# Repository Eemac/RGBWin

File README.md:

# RGBWin!!
A kW-scale RGBW LED controller for indoor effect lighting. I designed this board in my sophomore year of high school because no low-cost, highly-programmable RGBW solution existed at the time. The two TSSOP parts (PCA9685 16ch PWM controllers) were the first SMT parts I soldered. 

## Schematic
My second time using Autodesk Eagle. I didn't know pin labels were a thing, so all wires are directly routed from input to output. I'm so sorry! :P Also, an interesting story about the big power MOSFETs: the only ones I could find that were in my budget came from an obscure eBay listing. I ended up waiting about a month just to put the final parts on the board because shipping took so long! 

## PCB
A fairly decent design, I think. I didn't know about ground pours at the time, so I manually routed large ground traces to all of the power MOSFETs.

## Design Files/Code, should anyone want.
Provided in the `project` folder.
The Arduino code includes two libraries: `Thread` (https://www.arduino.cc/reference/en/libraries/thread/), and `PCA9685` (https://www.arduino.cc/reference/en/libraries/pca9685-16-channel-pwm-driver-module-library/). These two links have installation instructions and are supported by the Arduino Library manager.

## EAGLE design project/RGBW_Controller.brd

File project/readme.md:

# Project files

Eagle board/schematic files included as well as a test Arduino .ino file

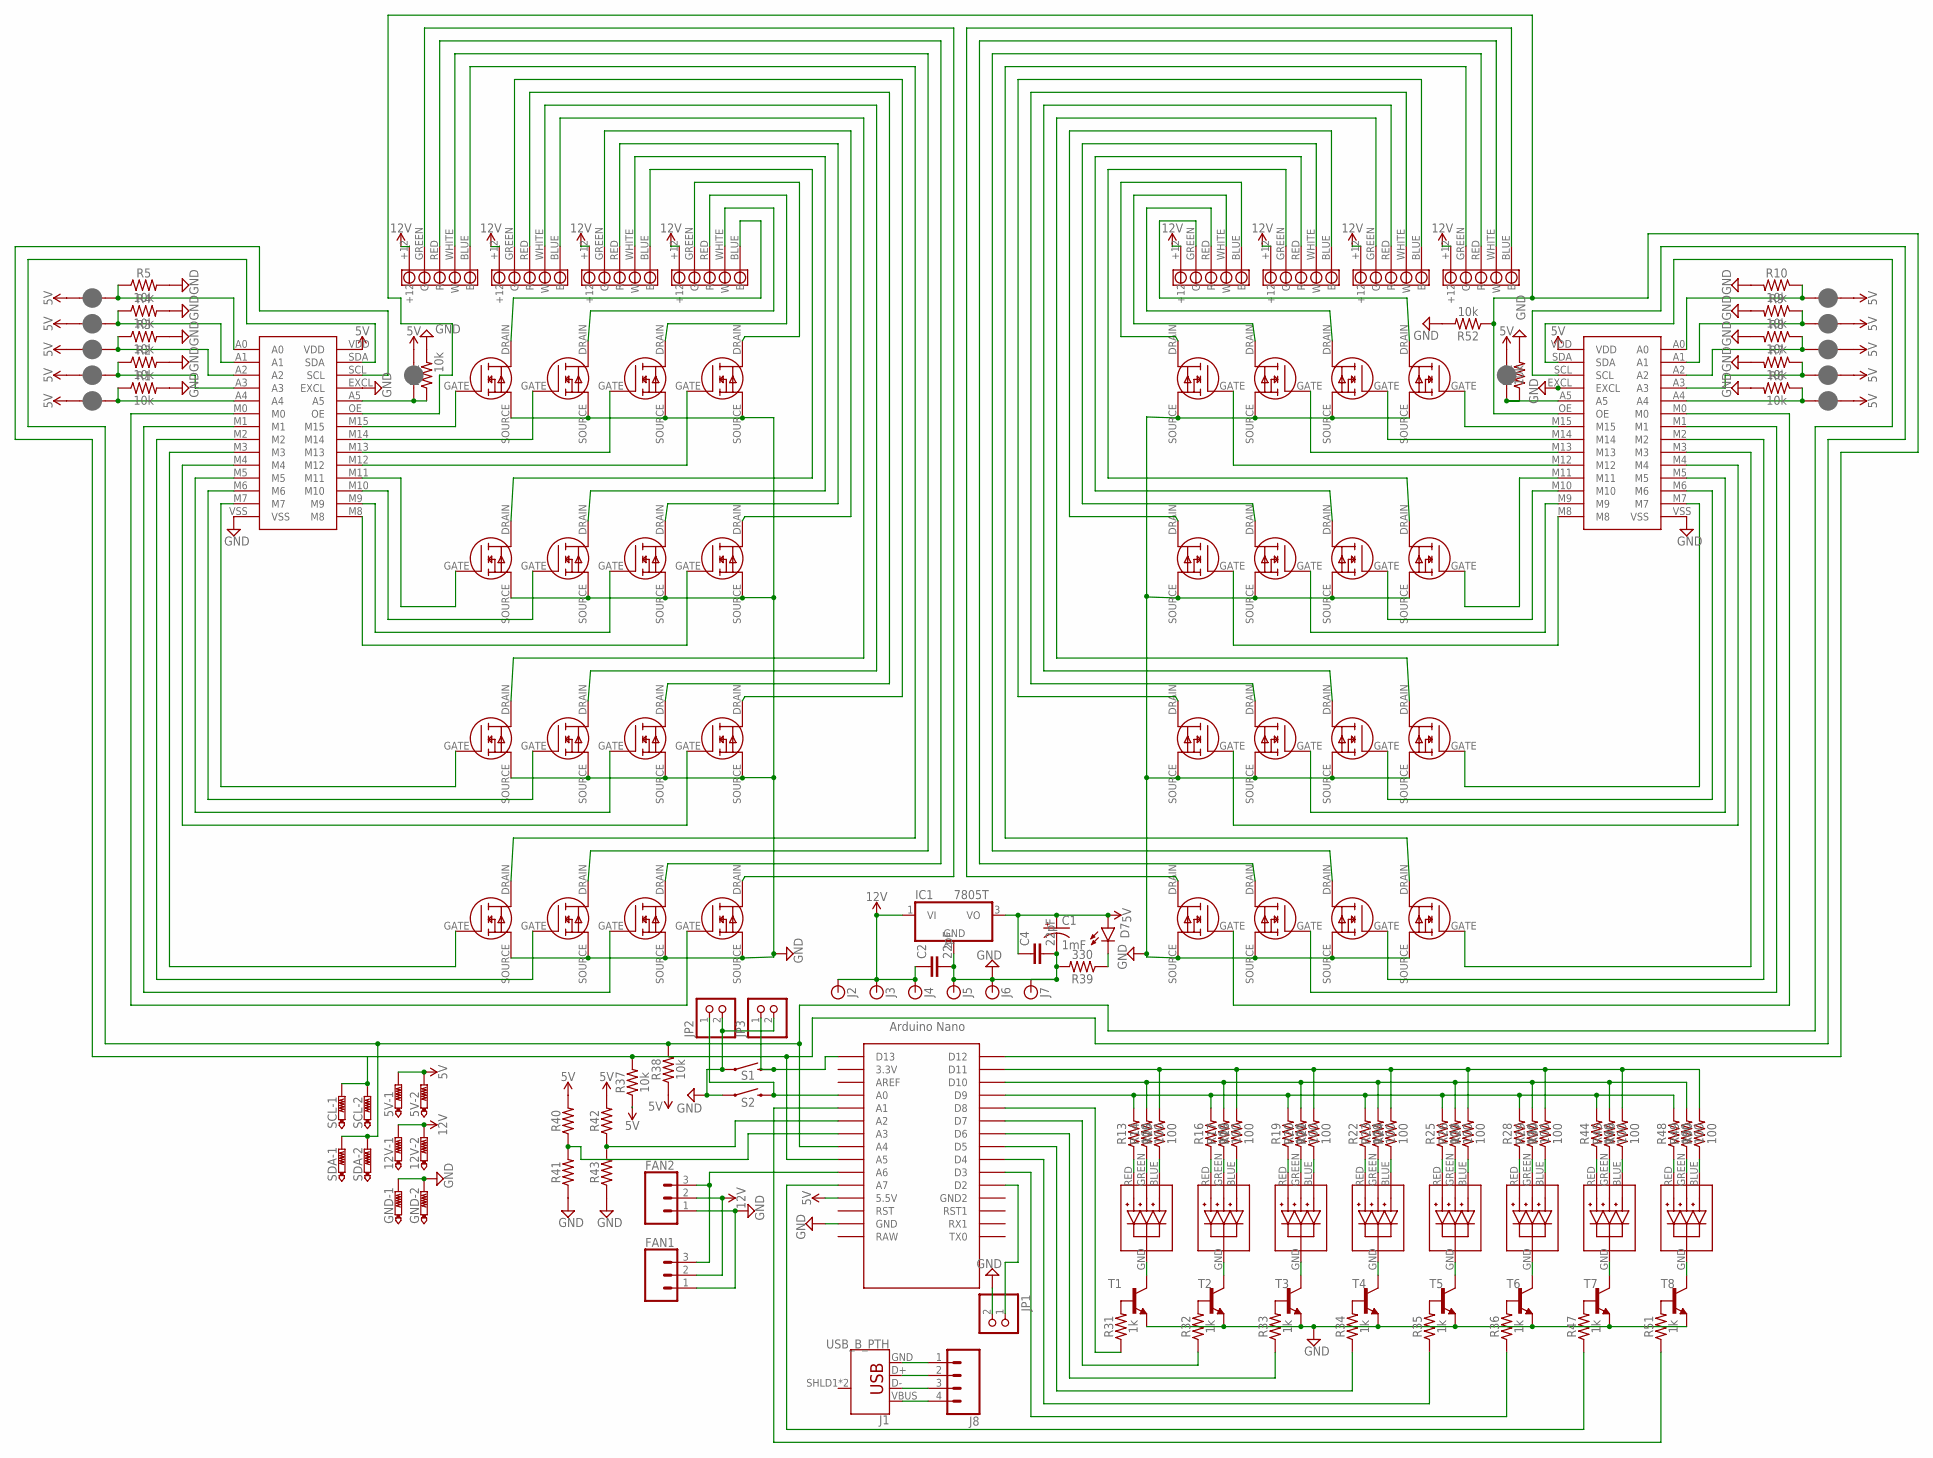
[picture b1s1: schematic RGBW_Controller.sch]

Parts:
5V, 12V: PTR2; P2-38-17
C1: 1mF; CPOL-RADIAL-5MM-10MM
C2, C4: 22pF; CAP-PTH-2.54
D7: LED5MM; LED_5MM
FAN1, FAN2: CONN_03; 1X03
GND: PTR2; P2-38-17
IC1: 7805T; TO220H
J1: USB_B_PTH; USB-B-PTH
J1_, J2_, J3_, J4_, J5_, J6_, J7_, J8_, J9_, J10_, J11_, J12_: JUMPER-SMT_2_NC_PASTE_SILK; SMT-JUMPER_2_NC_PASTE_SILK
J2, J3, J4, J5, J6, J7: BANANA_CONN
J8: CONN_04; 1X04
JP1, JP2, JP3: PINHD-1X2; 1X02
R1, R2, R3, R4, R5, R6, R7, R8, R9, R10, R11, R12, R37, R38, R52: 10k; AXIAL-0.3
R13, R14, R15, R16, R17, R18, R19, R20, R21, R22, R23, R24, R25, R26, R27, R28, R29, R30, R44, R45, R46, R48, R49, R50: 100; AXIAL-0.3
R31, R32, R33, R34, R35, R36, R47, R51: 1k; AXIAL-0.3
R39: 330; AXIAL-0.3
R40, R42: 10; AXIAL-0.1
R41, R43: 10; AXIAL-0.3
S1, S2: MOMENTARY-SWITCH-SPST-PTH-6.0MM; TACTILE_SWITCH_PTH_6.0MM
SCL: PTR2; P2-38-17
SDA: PTR2; P2-38-17
T1, T2, T3, T4, T5, T6, T7, T8: -NPN-TO92-EBC; TO92-EBC
U$1, U$18: 16CH_PWM
U$2, U$3, U$4, U$5, U$6, U$7, U$8, U$9, U$10, U$11, U$12, U$13, U$14, U$15, U$16, U$17, U$19, U$20, U$21, U$22, U$23, U$24, U$25, U$26, U$27, U$28, U$29, U$30, U$31, U$32, U$33, U$34: MOSFET
U$35: NANO
U$36, U$45, U$46, U$47, U$48, U$49, U$50, U$51: 5MM_RGB; 5MMRGB
U$37, U$38, U$39, U$40, U$41, U$42, U$43, U$44: 5POLE_TERM

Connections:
5V: 5V.TP-1, 5V.TP-2, C1.+, C4.1, D7.A, IC1.3 (VO), J1_.1, J2_.1, J3_.1, J4_.1, J5_.1, J6_.1, J7_.1, J8_.1, J9_.1, J10_.1, J11_.1, J12_.1, R37.P$1 (1), R38.P$1 (1), R40.P$2 (2), R42.P$2 (2), U$1.VDD, U$18.VDD, U$35.5V (5.5V)
12V: 12V.TP-1, 12V.TP-2, C2.1, FAN1.2, FAN2.2, IC1.1 (VI), J2.P$1, J3.P$1, J4.P$1, U$37.+12, U$38.+12, U$39.+12, U$40.+12, U$41.+12, U$42.+12, U$43.+12, U$44.+12
GND: C1.-, C2.2, C4.2, FAN1.1, FAN2.1, GND.TP-1, GND.TP-2, IC1.2 (GND), J5.P$1, J6.P$1, J7.P$1, JP1.2, JP2.2, JP3.2, R1.P$2 (2), R2.P$2 (2), R3.P$2 (2), R4.P$2 (2), R5.P$2 (2), R6.P$2 (2), R7.P$2 (2), R8.P$2 (2), R9.P$2 (2), R10.P$2 (2), R11.P$2 (2), R12.P$2 (2), R39.P$2 (2), R41.P$1 (1), R43.P$1 (1), R52.P$2 (2), S1.1, S2.1, T1.E, T2.E, T3.E, T4.E, T5.E, T6.E, T7.E, T8.E, U$1.EXCL, U$1.VSS, U$2.SOURCE, U$3.SOURCE, U$4.SOURCE, U$5.SOURCE, U$6.SOURCE, U$7.SOURCE, U$8.SOURCE, U$9.SOURCE, U$10.SOURCE, U$11.SOURCE, U$12.SOURCE, U$13.SOURCE, U$14.SOURCE, U$15.SOURCE, U$16.SOURCE, U$17.SOURCE, U$18.EXCL, U$18.VSS, U$19.SOURCE, U$20.SOURCE, U$21.SOURCE, U$22.SOURCE, U$23.SOURCE, U$24.SOURCE, U$25.SOURCE, U$26.SOURCE, U$27.SOURCE, U$28.SOURCE, U$29.SOURCE, U$30.SOURCE, U$31.SOURCE, U$32.SOURCE, U$33.SOURCE, U$34.SOURCE, U$35.GND
unnamed: J12_.2, R12.P$1 (1), U$18.A5
unnamed: R15.P$2 (2), R18.P$2 (2), R21.P$2 (2), R24.P$2 (2), R27.P$2 (2), R30.P$2 (2), R46.P$2 (2), R50.P$2 (2), U$35.D11
unnamed: R13.P$1 (1), U$36.RED
unnamed: R14.P$1 (1), U$36.GREEN
unnamed: J6_.2, R11.P$1 (1), U$1.A5
unnamed: R15.P$1 (1), U$36.BLUE
unnamed: U$18.M15, U$19.GATE
unnamed: U$18.M14, U$20.GATE
unnamed: U$18.M13, U$21.GATE
unnamed: U$1.M15, U$2.GATE
unnamed: U$1.M14, U$3.GATE
unnamed: U$1.M13, U$4.GATE
unnamed: U$1.M12, U$5.GATE
unnamed: D7.K (C), R39.P$1 (1)
unnamed: U$2.DRAIN, U$43.BLUE (B)
unnamed: R16.P$1 (1), U$45.RED
unnamed: R17.P$1 (1), U$45.GREEN
unnamed: J1_.2, R5.P$1 (1), U$1.A0
unnamed: U$1.M11, U$6.GATE
unnamed: U$1.M10, U$7.GATE
unnamed: U$1.M9, U$8.GATE
unnamed: U$1.M8, U$9.GATE
unnamed: R18.P$1 (1), U$45.BLUE
unnamed: R19.P$1 (1), U$46.RED
unnamed: R20.P$1 (1), U$46.GREEN
unnamed: R21.P$1 (1), U$46.BLUE
unnamed: U$18.M12, U$22.GATE
unnamed: U$1.M7, U$10.GATE
unnamed: U$1.M6, U$11.GATE
unnamed: U$1.M5, U$12.GATE
unnamed: U$1.M4, U$13.GATE
unnamed: R22.P$1 (1), U$47.RED
unnamed: R23.P$1 (1), U$47.GREEN
unnamed: R24.P$1 (1), U$47.BLUE
unnamed: R25.P$1 (1), U$48.RED
unnamed: U$22.DRAIN, U$44.BLUE (B)
unnamed: U$1.M3, U$14.GATE
unnamed: U$1.M2, U$15.GATE
unnamed: U$1.M1, U$16.GATE
unnamed: U$1.M0, U$17.GATE
unnamed: R26.P$1 (1), U$48.GREEN
unnamed: R27.P$1 (1), U$48.BLUE
unnamed: R28.P$1 (1), U$49.RED
unnamed: R29.P$1 (1), U$49.GREEN
unnamed: U$21.DRAIN, U$44.WHITE (W)
unnamed: U$20.DRAIN, U$44.RED (R)
unnamed: U$19.DRAIN, U$44.GREEN (G)
unnamed: J2_.2, R4.P$1 (1), U$1.A1
unnamed: U$18.M11, U$23.GATE
unnamed: U$18.M10, U$24.GATE
unnamed: U$18.M9, U$25.GATE
unnamed: U$18.M8, U$26.GATE
unnamed: U$26.DRAIN, U$42.BLUE (B)
unnamed: U$25.DRAIN, U$42.WHITE (W)
unnamed: U$24.DRAIN, U$42.RED (R)
unnamed: U$23.DRAIN, U$42.GREEN (G)
unnamed: U$18.M7, U$27.GATE
unnamed: U$18.M6, U$28.GATE
unnamed: U$18.M5, U$29.GATE
unnamed: U$18.M4, U$30.GATE
unnamed: U$30.DRAIN, U$41.BLUE (B)
unnamed: U$29.DRAIN, U$41.WHITE (W)
unnamed: U$28.DRAIN, U$41.RED (R)
unnamed: U$27.DRAIN, U$41.GREEN (G)
unnamed: U$18.M3, U$31.GATE
unnamed: U$18.M2, U$32.GATE
unnamed: U$18.M1, U$33.GATE
unnamed: U$18.M0, U$34.GATE
unnamed: U$34.DRAIN, U$40.BLUE (B)
unnamed: U$33.DRAIN, U$40.WHITE (W)
unnamed: U$32.DRAIN, U$40.RED (R)
unnamed: U$31.DRAIN, U$40.GREEN (G)
unnamed: R30.P$1 (1), U$49.BLUE
unnamed: JP3.1, S1.3 (2), U$35.D13
unnamed: JP2.1, S2.3 (2), U$35.A0
unnamed: T6.C, U$49.GND
unnamed: T5.C, U$48.GND
unnamed: T4.C, U$47.GND
unnamed: J3_.2, R3.P$1 (1), U$1.A2
unnamed: J4_.2, R2.P$1 (1), U$1.A3
unnamed: J5_.2, R1.P$1 (1), U$1.A4
unnamed: J7_.2, R10.P$1 (1), U$18.A0
unnamed: J8_.2, R9.P$1 (1), U$18.A1
unnamed: J9_.2, R8.P$1 (1), U$18.A2
unnamed: J10_.2, R7.P$1 (1), U$18.A3
unnamed: J11_.2, R6.P$1 (1), U$18.A4
unnamed: T3.C, U$46.GND
unnamed: T2.C, U$45.GND
unnamed: T1.C, U$36.GND
unnamed: J1.GND, J8.1
unnamed: J1.VBUS, J8.4
unnamed: J1.D-, J8.3
unnamed: J1.D+, J8.2
unnamed: R40.P$1 (1), R41.P$2 (2), U$35.A3
unnamed: R42.P$1 (1), R43.P$2 (2), U$35.A2
unnamed: FAN1.3, FAN2.3, U$35.A6
unnamed: R52.P$1 (1), U$1.OE, U$18.OE, U$35.D12
unnamed: R13.P$2 (2), R16.P$2 (2), R19.P$2 (2), R22.P$2 (2), R25.P$2 (2), R28.P$2 (2), R44.P$2 (2), R48.P$2 (2), U$35.D9
unnamed: JP1.1, U$35.D2
unnamed: R37.P$2 (2), SCL.TP-1, SCL.TP-2, U$1.SCL, U$18.SCL, U$35.A5
unnamed: R38.P$2 (2), SDA.TP-1, SDA.TP-2, U$1.SDA, U$18.SDA, U$35.A4
unnamed: R47.P$2 (2), T7.B
unnamed: R47.P$1 (1), U$35.A7
unnamed: R44.P$1 (1), U$50.RED
unnamed: R45.P$1 (1), U$50.GREEN
unnamed: R46.P$1 (1), U$50.BLUE
unnamed: R31.P$1 (1), U$35.D8
unnamed: R31.P$2 (2), T1.B
unnamed: R32.P$2 (2), T2.B
unnamed: R33.P$2 (2), T3.B
unnamed: R34.P$2 (2), T4.B
unnamed: R35.P$2 (2), T5.B
unnamed: R36.P$2 (2), T6.B
unnamed: R32.P$1 (1), U$35.D7
unnamed: R33.P$1 (1), U$35.D6
unnamed: R34.P$1 (1), U$35.D5
unnamed: R35.P$1 (1), U$35.D4
unnamed: R36.P$1 (1), U$35.D3
unnamed: U$17.DRAIN, U$37.GREEN (G)
unnamed: U$16.DRAIN, U$37.RED (R)
unnamed: U$15.DRAIN, U$37.WHITE (W)
unnamed: U$14.DRAIN, U$37.BLUE (B)
unnamed: T7.C, U$50.GND
unnamed: U$13.DRAIN, U$38.GREEN (G)
unnamed: U$12.DRAIN, U$38.RED (R)
unnamed: U$11.DRAIN, U$38.WHITE (W)
unnamed: U$10.DRAIN, U$38.BLUE (B)
unnamed: U$9.DRAIN, U$39.GREEN (G)
unnamed: U$8.DRAIN, U$39.RED (R)
unnamed: U$7.DRAIN, U$39.WHITE (W)
unnamed: U$6.DRAIN, U$39.BLUE (B)
unnamed: U$5.DRAIN, U$43.GREEN (G)
unnamed: U$4.DRAIN, U$43.RED (R)
unnamed: U$3.DRAIN, U$43.WHITE (W)
unnamed: R14.P$2 (2), R17.P$2 (2), R20.P$2 (2), R23.P$2 (2), R26.P$2 (2), R29.P$2 (2), R45.P$2 (2), R49.P$2 (2), U$35.D10
unnamed: R51.P$2 (2), T8.B
unnamed: R51.P$1 (1), U$35.A1
unnamed: R48.P$1 (1), U$51.RED
unnamed: R49.P$1 (1), U$51.GREEN
unnamed: R50.P$1 (1), U$51.BLUE
unnamed: T8.C, U$51.GND

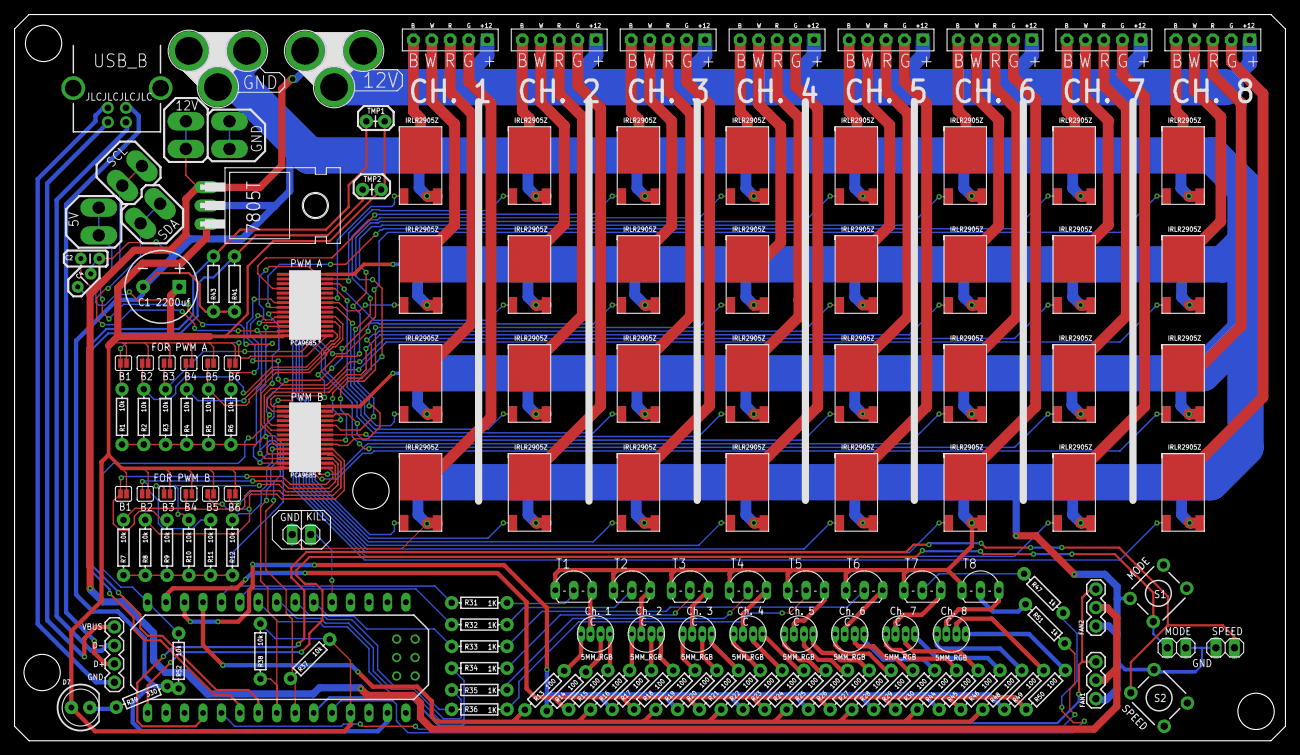
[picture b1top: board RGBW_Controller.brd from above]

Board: 2 copper layers, 175.0 x 100.0 mm, 148 parts (0 on the bottom side), 144 nets.

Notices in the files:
parts and their libraries:
SparkFun-Connectors: Licensing: Creative Commons ShareAlike 4.0 International - https://creativecommons.org/licenses/by-sa/4.0
